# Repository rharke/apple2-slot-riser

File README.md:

# Apple II Card Slot Riser

This is a simple KiCad project to build an Apple II card slot riser.

It contains mounting points for straddle-mounting an edge connector, or using a right-angle connector.

It also contains a spot to mount a 50 pin header for connection to a logic analyzer or something else like a slot extender.

Only the +5V power line is connected; +12, -12, and -5 are unconnected for safety. But adding them back would be trivial if you need them.

# License

Copyright 2020 Renee Harke

Permission is hereby granted, free of charge, to any person obtaining a copy of this software and associated documentation files (the "Software"), to deal in the Software without restriction, including without limitation the rights to use, copy, modify, merge, publish, distribute, sublicense, and/or sell copies of the Software, and to permit persons to whom the Software is furnished to do so, subject to the following conditions:

The above copyright notice and this permission notice shall be included in all copies or substantial portions of the Software.

THE SOFTWARE IS PROVIDED "AS IS", WITHOUT WARRANTY OF ANY KIND, EXPRESS OR IMPLIED, INCLUDING BUT NOT LIMITED TO THE WARRANTIES OF MERCHANTABILITY, FITNESS FOR A PARTICULAR PURPOSE AND NONINFRINGEMENT. IN NO EVENT SHALL THE AUTHORS OR COPYRIGHT HOLDERS BE LIABLE FOR ANY CLAIM, DAMAGES OR OTHER LIABILITY, WHETHER IN AN ACTION OF CONTRACT, TORT OR OTHERWISE, ARISING FROM, OUT OF OR IN CONNECTION WITH THE SOFTWARE OR THE USE OR OTHER DEALINGS IN THE SOFTWARE.

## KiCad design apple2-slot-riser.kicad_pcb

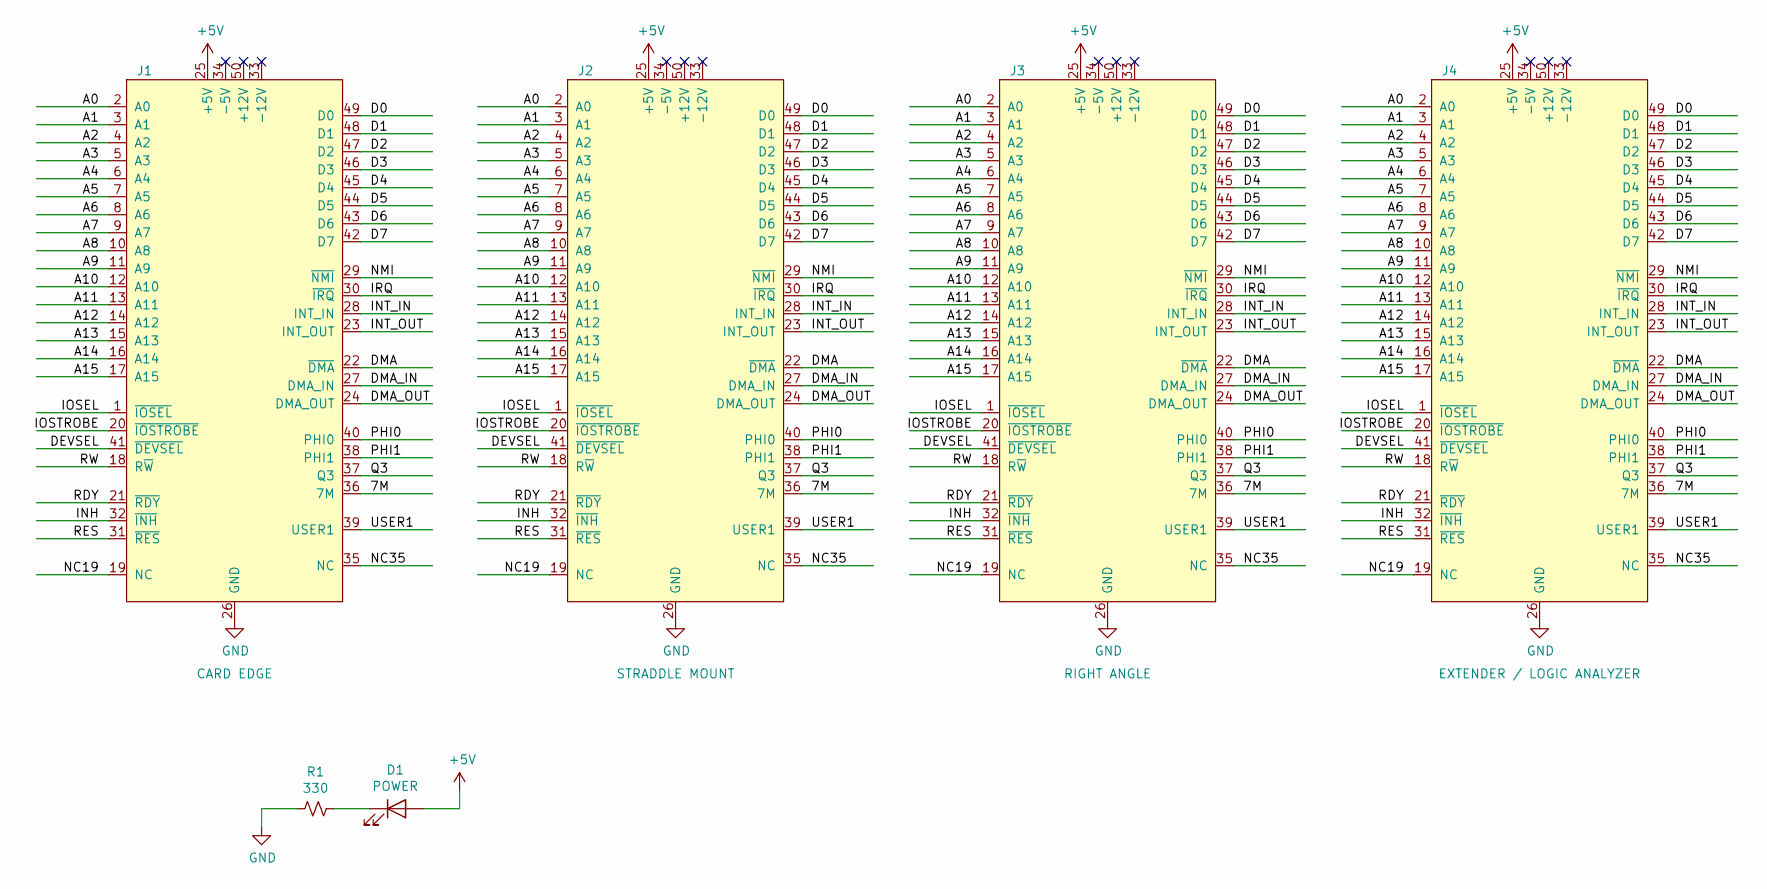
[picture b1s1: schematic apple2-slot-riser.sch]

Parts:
D1: POWER; LED_D5.0mm
J1: CARD EDGE; AppleIIBus
J2: STRADDLE MOUNT; AppleIIBus_TightMask
J3: RIGHT ANGLE; CardEdge_EDEC_3x5-050_2x25_P2.54mm_CCW
J4: EXTENDER / LOGIC ANALYZER; IDC-Header_2x25_P2.54mm_Vertical_CCW
R1: 330; R_Axial_DIN0207_L6.3mm_D2.5mm_P10.16mm_Horizontal

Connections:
+5V: D1.2 (A), J1.25 (+5V), J2.25 (+5V), J3.25 (+5V), J4.25 (+5V)
/7M: J1.36 (7M), J2.36 (7M), J3.36 (7M), J4.36 (7M)
/A0: J1.2 (A0), J2.2 (A0), J3.2 (A0), J4.2 (A0)
/A1: J1.3 (A1), J2.3 (A1), J3.3 (A1), J4.3 (A1)
/A2: J1.4 (A2), J2.4 (A2), J3.4 (A2), J4.4 (A2)
/A3: J1.5 (A3), J2.5 (A3), J3.5 (A3), J4.5 (A3)
/A4: J1.6 (A4), J2.6 (A4), J3.6 (A4), J4.6 (A4)
/A5: J1.7 (A5), J2.7 (A5), J3.7 (A5), J4.7 (A5)
/A6: J1.8 (A6), J2.8 (A6), J3.8 (A6), J4.8 (A6)
/A7: J1.9 (A7), J2.9 (A7), J3.9 (A7), J4.9 (A7)
/A8: J1.10 (A8), J2.10 (A8), J3.10 (A8), J4.10 (A8)
/A9: J1.11 (A9), J2.11 (A9), J3.11 (A9), J4.11 (A9)
/A10: J1.12 (A10), J2.12 (A10), J3.12 (A10), J4.12 (A10)
/A11: J1.13 (A11), J2.13 (A11), J3.13 (A11), J4.13 (A11)
/A12: J1.14 (A12), J2.14 (A12), J3.14 (A12), J4.14 (A12)
/A13: J1.15 (A13), J2.15 (A13), J3.15 (A13), J4.15 (A13)
/A14: J1.16 (A14), J2.16 (A14), J3.16 (A14), J4.16 (A14)
/A15: J1.17 (A15), J2.17 (A15), J3.17 (A15), J4.17 (A15)
/D0: J1.49 (D0), J2.49 (D0), J3.49 (D0), J4.49 (D0)
/D1: J1.48 (D1), J2.48 (D1), J3.48 (D1), J4.48 (D1)
/D2: J1.47 (D2), J2.47 (D2), J3.47 (D2), J4.47 (D2)
/D3: J1.46 (D3), J2.46 (D3), J3.46 (D3), J4.46 (D3)
/D4: J1.45 (D4), J2.45 (D4), J3.45 (D4), J4.45 (D4)
/D5: J1.44 (D5), J2.44 (D5), J3.44 (D5), J4.44 (D5)
/D6: J1.43 (D6), J2.43 (D6), J3.43 (D6), J4.43 (D6)
/D7: J1.42 (D7), J2.42 (D7), J3.42 (D7), J4.42 (D7)
/DEVSEL: J1.41 (~DEVSEL), J2.41 (~DEVSEL), J3.41 (~DEVSEL), J4.41 (~DEVSEL)
/DMA: J1.22 (~DMA), J2.22 (~DMA), J3.22 (~DMA), J4.22 (~DMA)
/DMA_IN: J1.27 (DMA_IN), J2.27 (DMA_IN), J3.27 (DMA_IN), J4.27 (DMA_IN)
/DMA_OUT: J1.24 (DMA_OUT), J2.24 (DMA_OUT), J3.24 (DMA_OUT), J4.24 (DMA_OUT)
/INH: J1.32 (~INH), J2.32 (~INH), J3.32 (~INH), J4.32 (~INH)
/INT_IN: J1.28 (INT_IN), J2.28 (INT_IN), J3.28 (INT_IN), J4.28 (INT_IN)
/INT_OUT: J1.23 (INT_OUT), J2.23 (INT_OUT), J3.23 (INT_OUT), J4.23 (INT_OUT)
/IOSEL: J1.1 (~IOSEL), J2.1 (~IOSEL), J3.1 (~IOSEL), J4.1 (~IOSEL)
/IOSTROBE: J1.20 (~IOSTROBE), J2.20 (~IOSTROBE), J3.20 (~IOSTROBE), J4.20 (~IOSTROBE)
/IRQ: J1.30 (~IRQ), J2.30 (~IRQ), J3.30 (~IRQ), J4.30 (~IRQ)
/NC19: J1.19 (NC), J2.19 (NC), J3.19 (NC), J4.19 (NC)
/NC35: J1.35 (NC), J2.35 (NC), J3.35 (NC), J4.35 (NC)
/NMI: J1.29 (~NMI), J2.29 (~NMI), J3.29 (~NMI), J4.29 (~NMI)
/PHI0: J1.40 (PHI0), J2.40 (PHI0), J3.40 (PHI0), J4.40 (PHI0)
/PHI1: J1.38 (PHI1), J2.38 (PHI1), J3.38 (PHI1), J4.38 (PHI1)
/Q3: J1.37 (Q3), J2.37 (Q3), J3.37 (Q3), J4.37 (Q3)
/RDY: J1.21 (~RDY), J2.21 (~RDY), J3.21 (~RDY), J4.21 (~RDY)
/RES: J1.31 (~RES), J2.31 (~RES), J3.31 (~RES), J4.31 (~RES)
/RW: J1.18 (R~W), J2.18 (R~W), J3.18 (R~W), J4.18 (R~W)
/USER1: J1.39 (USER1), J2.39 (USER1), J3.39 (USER1), J4.39 (USER1)
GND: J1.26 (GND), J2.26 (GND), J3.26 (GND), J4.26 (GND), R1.2
unnamed: D1.1 (K), R1.1

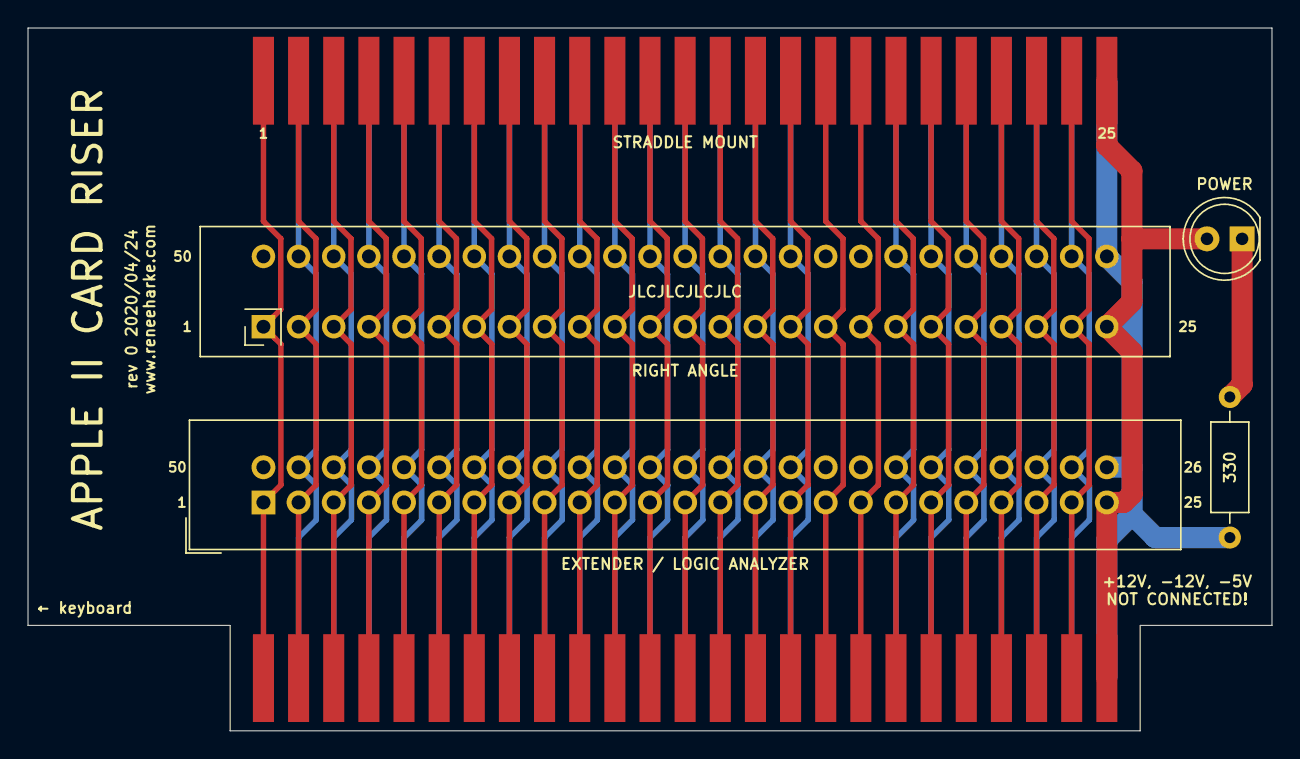
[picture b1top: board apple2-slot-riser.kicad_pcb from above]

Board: 2 copper layers, 89.9 x 50.8 mm, 6 parts (0 on the bottom side), 48 nets.

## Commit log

2020-08-18 Add readme and license
2020-08-18 Add image
